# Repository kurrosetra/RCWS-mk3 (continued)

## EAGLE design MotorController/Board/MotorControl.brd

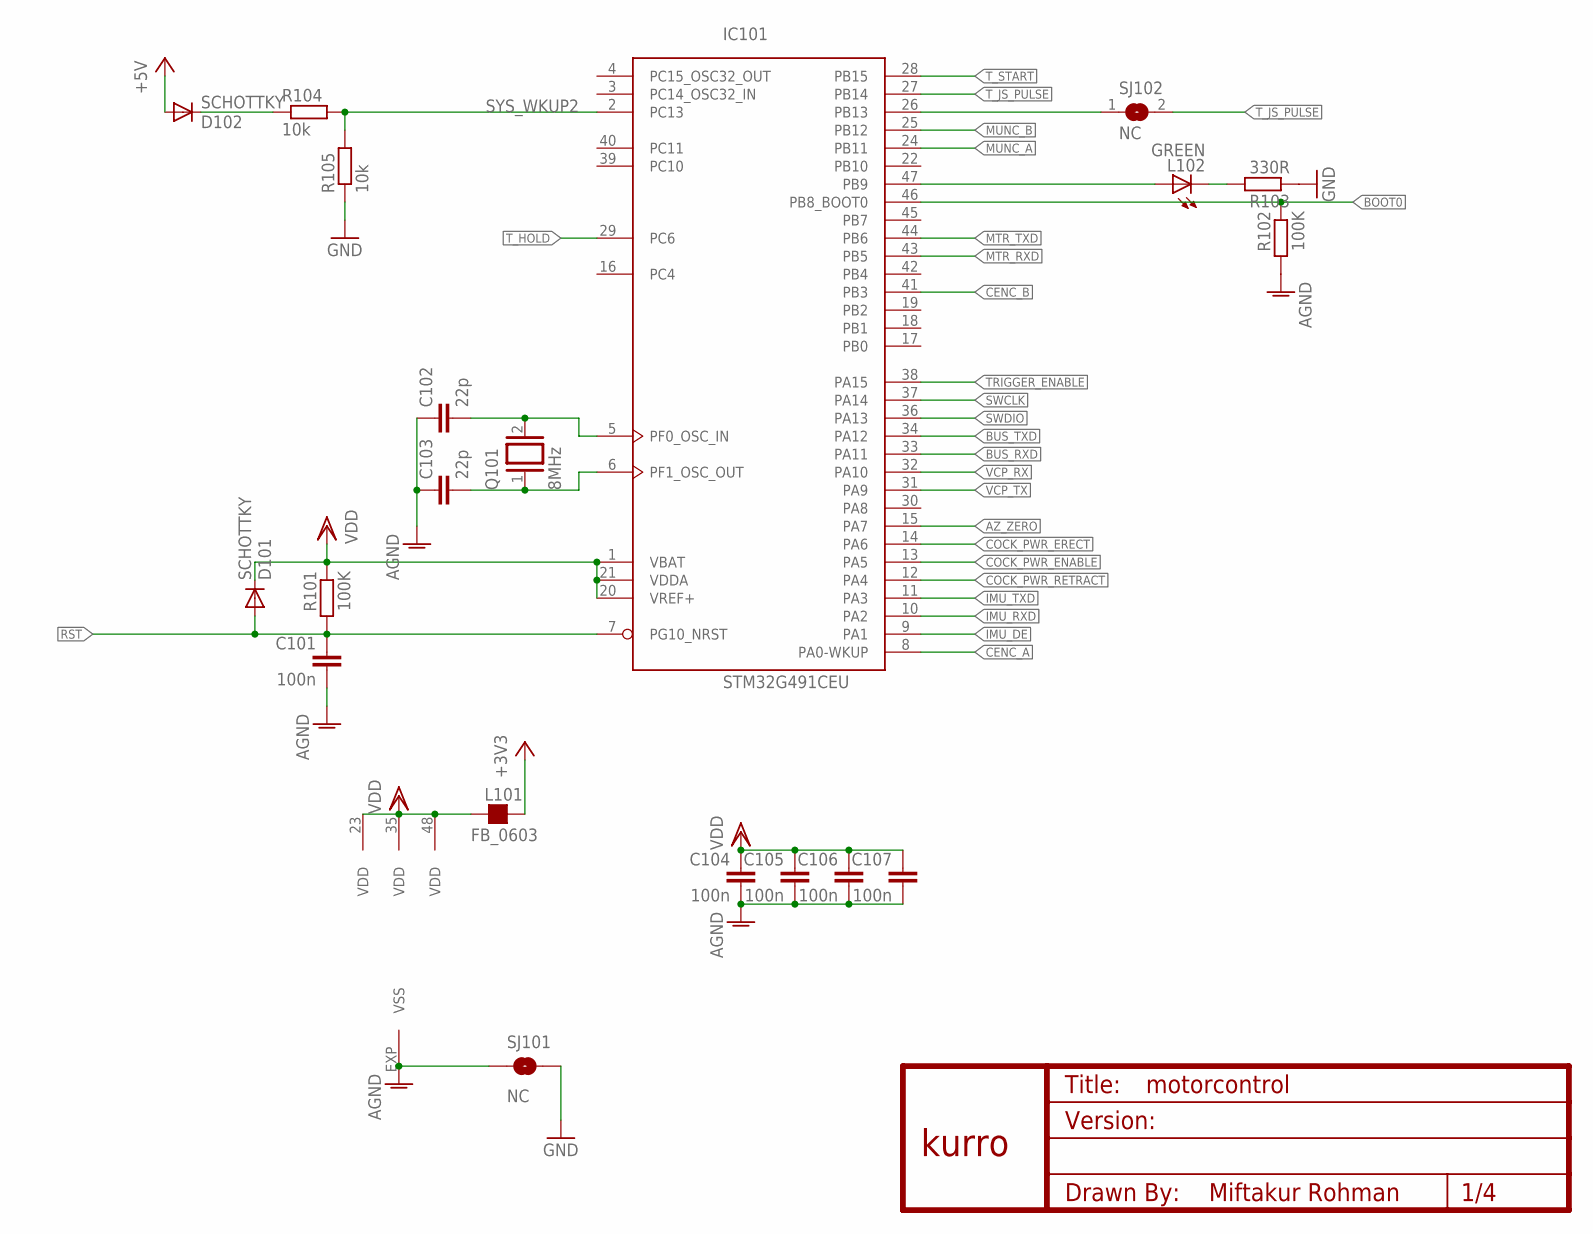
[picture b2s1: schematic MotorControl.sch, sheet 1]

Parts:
C101, C104, C105, C106, C107: 100n; C0603
C102, C103: 22p; C0603
D101, D102: SCHOTTKY; MICROMELF-W
IC101: STM32G491CEU; UFQFPN48
L101: FB_0603; L0603
L102: GREEN; CHIP-LED0805
Q101: 8MHz; QS
R101, R102: 100K; R0603
R103: 330R; R0603
R104, R105: 10k; R0603
SJ101: NC; SJ_2S-TRACE_THICK
SJ102: NC; SJS
U$1: KURRO_FOOTPRINT; KURRO-LOGO

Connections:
!RST: C101.1, D101.A, IC101.7 (PG10_NRST), R101.2; also elsewhere on the board
+3V3: L101.2; also elsewhere on the board
+5V: D102.A; also elsewhere on the board
AGND: C101.2, C102.1, C103.1, C104.2, C105.2, C106.2, C107.2, IC101.EXP (VSS), R102.2, SJ101.1
AZ_ZERO: IC101.15 (PA7); also elsewhere on the board
BOOT0: IC101.46 (PB8_BOOT0), R102.1; also elsewhere on the board
BUS_RXD: IC101.33 (PA11); also elsewhere on the board
BUS_TXD: IC101.34 (PA12); also elsewhere on the board
CENC_A: IC101.8 (PA0-WKUP); also elsewhere on the board
CENC_B: IC101.41 (PB3); also elsewhere on the board
COCK_PWR_ENABLE: IC101.13 (PA5); also elsewhere on the board
COCK_PWR_ERECT: IC101.14 (PA6); also elsewhere on the board
COCK_PWR_RETRACT: IC101.12 (PA4); also elsewhere on the board
GND: R103.1, R105.1, SJ101.2; also elsewhere on the board
IMU_DE: IC101.9 (PA1); also elsewhere on the board
IMU_RXD: IC101.10 (PA2); also elsewhere on the board
IMU_TXD: IC101.11 (PA3); also elsewhere on the board
MTR_RXD: IC101.43 (PB5); also elsewhere on the board
MTR_TXD: IC101.44 (PB6); also elsewhere on the board
MUNC_A: IC101.24 (PB11); also elsewhere on the board
MUNC_B: IC101.25 (PB12); also elsewhere on the board
unnamed: IC101.47 (PB9), L102.A
unnamed: L102.C, R103.2
unnamed: D102.C, R104.1
unnamed: C103.2, IC101.6 (PF1_OSC_OUT), Q101.1
unnamed: IC101.26 (PB13), SJ102.1
unnamed: C102.2, IC101.5 (PF0_OSC_IN), Q101.2
SWCLK: IC101.37 (PA14); also elsewhere on the board
SWDIO: IC101.36 (PA13); also elsewhere on the board
SYS_WKUP2: IC101.2 (PC13), R104.2, R105.2
TRIGGER_ENABLE: IC101.38 (PA15); also elsewhere on the board
T_HOLD: IC101.29 (PC6); also elsewhere on the board
T_JS_PULSE: IC101.27 (PB14), SJ102.2; also elsewhere on the board
T_START: IC101.28 (PB15); also elsewhere on the board
VCP_RX: IC101.32 (PA10); also elsewhere on the board
VCP_TX: IC101.31 (PA9); also elsewhere on the board
VDD: C104.1, C105.1, C106.1, C107.1, D101.C, IC101.1 (VBAT), IC101.20 (VREF+), IC101.21 (VDDA), IC101.23 (VDD), IC101.35 (VDD), IC101.48 (VDD), L101.1, R101.1; also elsewhere on the board

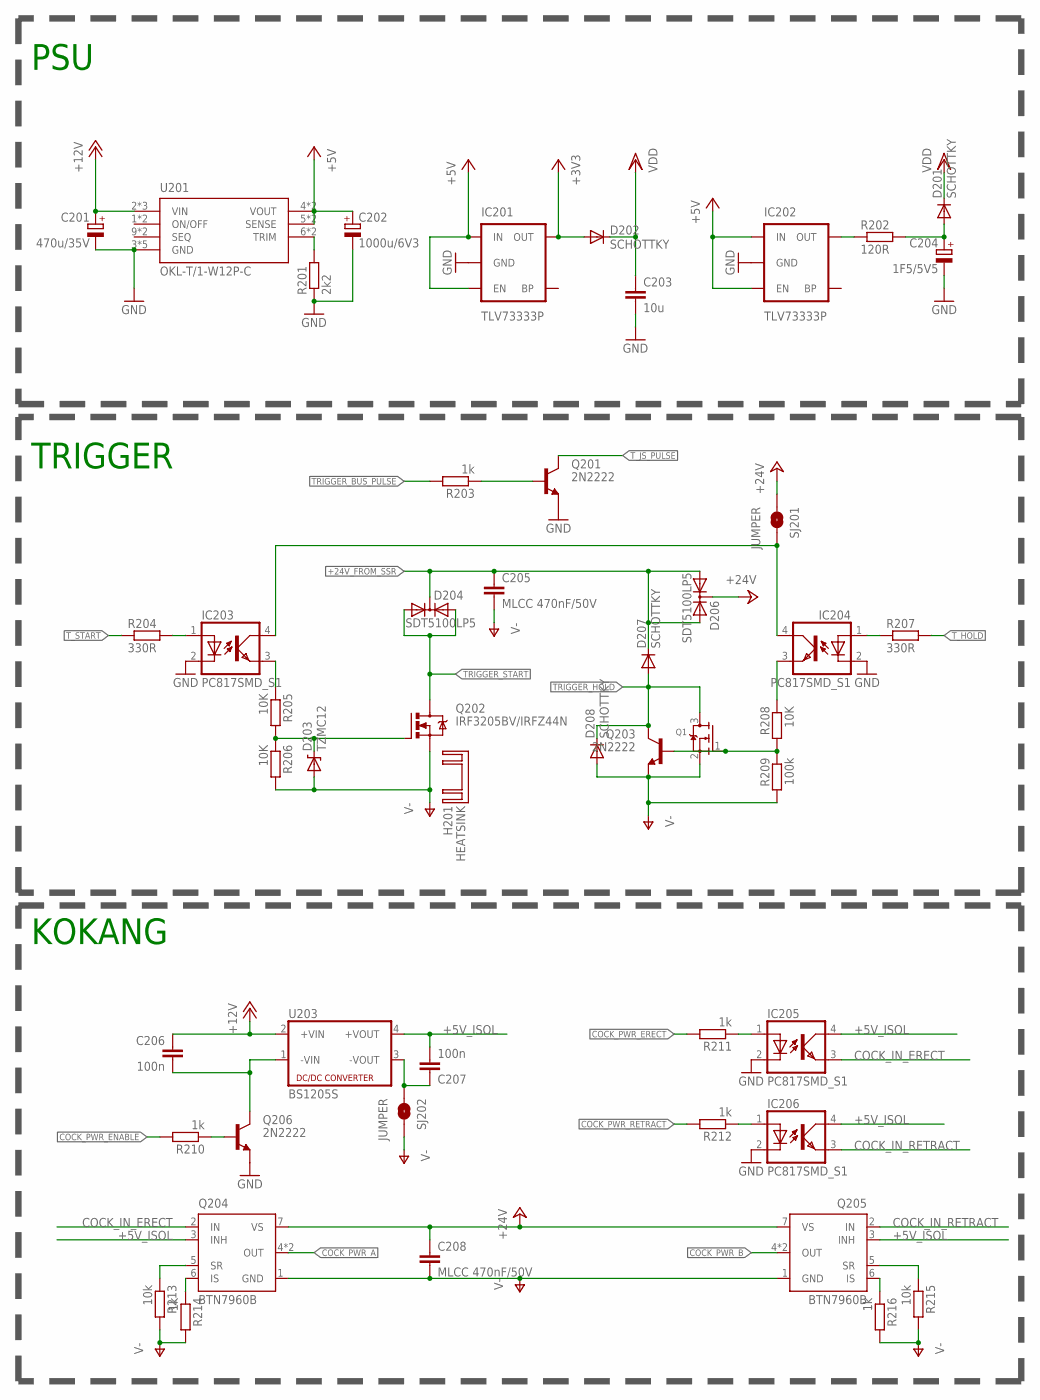
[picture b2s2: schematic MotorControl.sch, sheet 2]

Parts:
C201: 470u/35V; 153CLV-1012
C202: 1000u/6V3; 153CLV-0810
C203: 10u; C0805
C204: 1F5/5V5; SC_1F/5V5
C205, C208: MLCC 470nF/50V; C150-064X183
C206, C207: 100n; C0603
D201, D202, D207, D208: SCHOTTKY; MICROMELF-W
D203: TZMC12; SMB-DIODE
D204, D206: SDT5100LP5; POWERDI5-3
H201: HEATSINK; BV_240X170-HOLE
IC201, IC202: TLV73333P; SOT23-5
IC203, IC204, IC205, IC206: PC817SMD_S1; PC817SMD
Q1: AO3404-REFLOW; SOT23
Q201, Q203, Q206: 2N2222; SOT23
Q202: IRF3205BV/IRFZ44N; TO220BV
Q204: BTN7960B; PG-TO263-7-1; PARTNO BTN7960B
Q205: BTN7960B; PG-TO263-7-1
R201: 2k2; R0603
R202: 120R; R0603
R203, R210, R211, R212, R214, R216: 1k; R0603
R204, R207: 330R; R0603
R205, R206, R208: 10K; R0603
R209: 100k; R0603
R213, R215: 10k; R0603
SJ201, SJ202: JUMPER; SJ_2S-TRACE_THICK
U201: OKL-T/1-W12P-C; OKL2T/3W5NC
U203: BS1205S; NME

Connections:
+3V3: D202.A, IC201.5 (OUT); also elsewhere on the board
+5V: C202.+, IC201.1 (IN), IC201.3 (EN), IC202.1 (IN), IC202.3 (EN), U201.4 (VOUT), U201.4@1 (VOUT), U201.5 (SENSE), U201.5@1 (SENSE); also elsewhere on the board
+5V_ISOL: C207.2, IC205.4 (COL), IC206.4 (COL), Q204.3 (INH), Q205.3 (INH), U203.4 (+VOUT)
+12V: C201.+, C206.1, U201.2 (VIN), U201.2@1 (VIN), U201.2@2 (VIN), U203.2 (+VIN); also elsewhere on the board
+24V: C208.1, D206.3, Q204.7 (VS), Q205.7 (VS), SJ201.1; also elsewhere on the board
+24V_FROM_SSR: C205.1, D204.3, D206.1, D206.2, D207.C; also elsewhere on the board
COCK_IN_ERECT: IC205.3 (EMIT), Q204.2 (IN)
COCK_IN_RETRACT: IC206.3 (EMIT), Q205.2 (IN)
COCK_PWR_A: Q204.4 (OUT), Q204.8 (OUT); also elsewhere on the board
COCK_PWR_B: Q205.4 (OUT), Q205.8 (OUT); also elsewhere on the board
COCK_PWR_ENABLE: R210.2; also elsewhere on the board
COCK_PWR_ERECT: R211.2; also elsewhere on the board
COCK_PWR_RETRACT: R212.2; also elsewhere on the board
COCK_SENSOR1: Q204.6 (IS), R214.1
GND: C201.-, C202.-, C203.2, C204.2 (-), IC201.2 (GND), IC202.2 (GND), IC203.2 (C), IC204.2 (C), IC205.2 (C), IC206.2 (C), Q201.2 (E), Q206.2 (E), R201.1, U201.3 (GND), U201.3@1 (GND), U201.3@2 (GND), U201.7 (GND), U201.7@1 (GND); also elsewhere on the board
unnamed: IC203.4 (COL), IC204.4 (COL), SJ201.2
unnamed: Q204.5 (SR), R213.1
unnamed: Q205.5 (SR), R215.1
unnamed: Q205.6 (IS), R216.1
unnamed: Q206.1 (B), R210.1
unnamed: C206.2, Q206.3 (C), U203.1 (-VIN)
unnamed: Q201.1 (B), R203.1
unnamed: IC205.1 (A), R211.1
unnamed: R201.2, U201.6 (TRIM), U201.6@1 (TRIM)
unnamed: IC206.1 (A), R212.1
unnamed: C207.1, SJ202.1, U203.3 (-VOUT)
unnamed: D203.C, Q202.G, R205.2, R206.1
unnamed: Q1.1 (G), Q203.1 (B), R208.2, R209.1
unnamed: IC203.3 (EMIT), R205.1
unnamed: IC204.3 (EMIT), R208.1
unnamed: IC204.1 (A), R207.1
unnamed: IC203.1 (A), R204.2
unnamed: IC202.5 (OUT), R202.1
TRIGGER_BUS_PULSE: R203.2; also elsewhere on the board
TRIGGER_HOLD: D207.A, D208.C, Q1.3 (D), Q203.3 (C); also elsewhere on the board
TRIGGER_START: D204.1, D204.2, Q202.D; also elsewhere on the board
T_HOLD: R207.2; also elsewhere on the board
T_JS_PULSE: Q201.3 (C); also elsewhere on the board
T_START: R204.1; also elsewhere on the board
V-: C205.2, C208.2, D203.A, D208.A, Q1.2 (S), Q202.S, Q203.2 (E), Q204.1 (GND), Q205.1 (GND), R206.2, R209.2, R213.2, R214.2, R215.2, R216.2, SJ202.2; also elsewhere on the board
VDD: C203.1, D201.C, D202.C; also elsewhere on the board
V_SCAP: C204.1 (+), D201.A, R202.2

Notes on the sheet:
KOKANG
TRIGGER
PSU

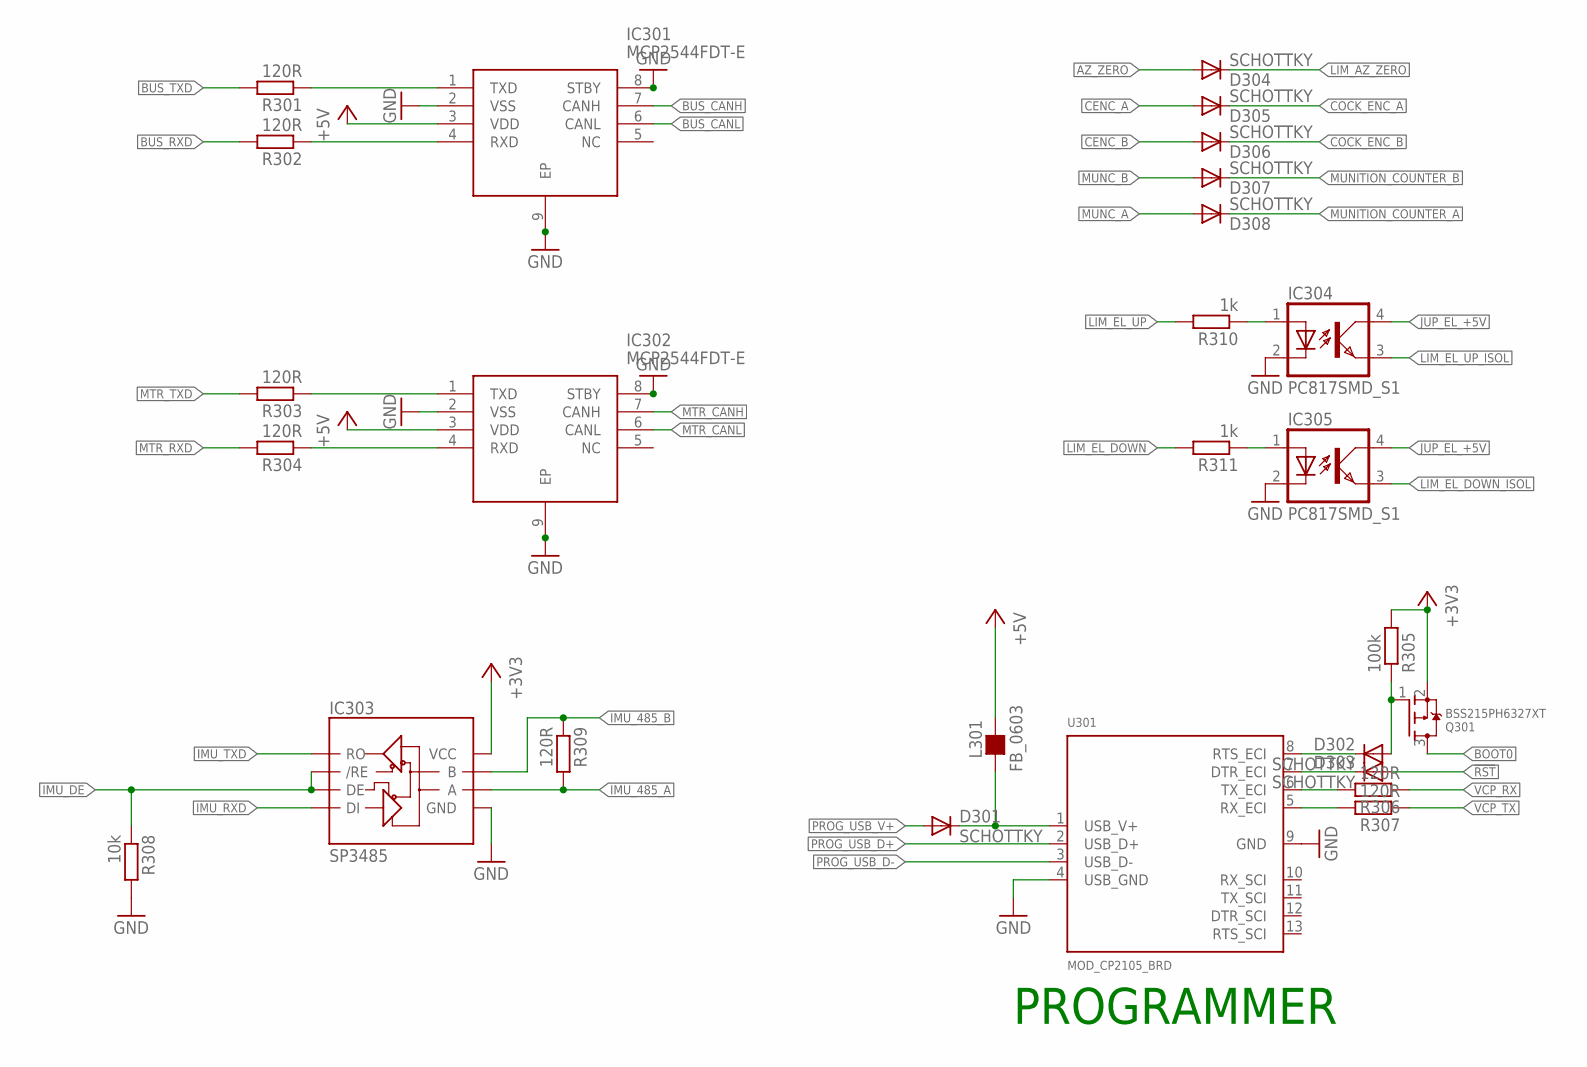
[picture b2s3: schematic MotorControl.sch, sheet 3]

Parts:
D301, D302, D303, D304, D305, D306, D307, D308: SCHOTTKY; MICROMELF-W
IC301, IC302: MCP2544FDT-E; TDFN-8
IC303: SP3485; SO08
IC304, IC305: PC817SMD_S1; PC817SMD
L301: FB_0603; L0603
Q301: BSS215PH6327XT; SOT23-W
R301, R302, R303, R304, R306, R307, R309: 120R; R0603
R305: 100k; R0603
R308: 10k; R0603
R310, R311: 1k; R0603
U301: MOD_CP2105_BRD; MOD_CP2105_BOARD

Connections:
!RST: D303.A; also elsewhere on the board
+3V3: IC303.8 (VCC), Q301.2 (S), R305.2; also elsewhere on the board
+5V: IC301.3 (VDD), IC302.3 (VDD), L301.2; also elsewhere on the board
AZ_ZERO: D304.A; also elsewhere on the board
BOOT0: Q301.3 (D); also elsewhere on the board
BUS_CANH: IC301.7 (CANH); also elsewhere on the board
BUS_CANL: IC301.6 (CANL); also elsewhere on the board
BUS_RXD: R302.2; also elsewhere on the board
BUS_TXD: R301.2; also elsewhere on the board
CENC_A: D305.A; also elsewhere on the board
CENC_B: D306.A; also elsewhere on the board
COCK_ENC_A: D305.C; also elsewhere on the board
COCK_ENC_B: D306.C; also elsewhere on the board
GND: IC301.2 (VSS), IC301.8 (STBY), IC301.9 (EP), IC302.2 (VSS), IC302.8 (STBY), IC302.9 (EP), IC303.5 (GND), IC304.2 (C), IC305.2 (C), R308.2, U301.4 (USB_GND), U301.9 (GND); also elsewhere on the board
IMU_485_A: IC303.6 (A), R309.2; also elsewhere on the board
IMU_485_B: IC303.7 (B), R309.1; also elsewhere on the board
IMU_DE: IC303.2 (/RE), IC303.3 (DE), R308.1; also elsewhere on the board
IMU_RXD: IC303.4 (DI); also elsewhere on the board
IMU_TXD: IC303.1 (RO); also elsewhere on the board
JUP_EL_+5V: IC304.4 (COL), IC305.4 (COL); also elsewhere on the board
LIM_AZ_ZERO: D304.C; also elsewhere on the board
LIM_EL_DOWN: R311.2; also elsewhere on the board
LIM_EL_DOWN_ISOL: IC305.3 (EMIT); also elsewhere on the board
LIM_EL_UP: R310.2; also elsewhere on the board
LIM_EL_UP_ISOL: IC304.3 (EMIT); also elsewhere on the board
MTR_CANH: IC302.7 (CANH); also elsewhere on the board
MTR_CANL: IC302.6 (CANL); also elsewhere on the board
MTR_RXD: R304.2; also elsewhere on the board
MTR_TXD: R303.2; also elsewhere on the board
MUNC_A: D308.A; also elsewhere on the board
MUNC_B: D307.A; also elsewhere on the board
MUNITION_COUNTER_A: D308.C; also elsewhere on the board
MUNITION_COUNTER_B: D307.C; also elsewhere on the board
unnamed: IC304.1 (A), R310.1
unnamed: R307.2, U301.5 (RX_ECI)
unnamed: R306.2, U301.6 (TX_ECI)
unnamed: D303.C, U301.7 (DTR_ECI)
unnamed: D302.C, U301.8 (RTS_ECI)
unnamed: D301.C, L301.1, U301.1 (USB_V+)
unnamed: D302.A, Q301.1 (G), R305.1
unnamed: IC305.1 (A), R311.1
unnamed: IC301.4 (RXD), R302.1
unnamed: IC301.1 (TXD), R301.1
unnamed: IC302.4 (RXD), R304.1
unnamed: IC302.1 (TXD), R303.1
PROG_USB_D+: U301.2 (USB_D+); also elsewhere on the board
PROG_USB_D-: U301.3 (USB_D-); also elsewhere on the board
PROG_USB_V+: D301.A; also elsewhere on the board
VCP_RX: R306.1; also elsewhere on the board
VCP_TX: R307.1; also elsewhere on the board

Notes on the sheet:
PROGRAMMER

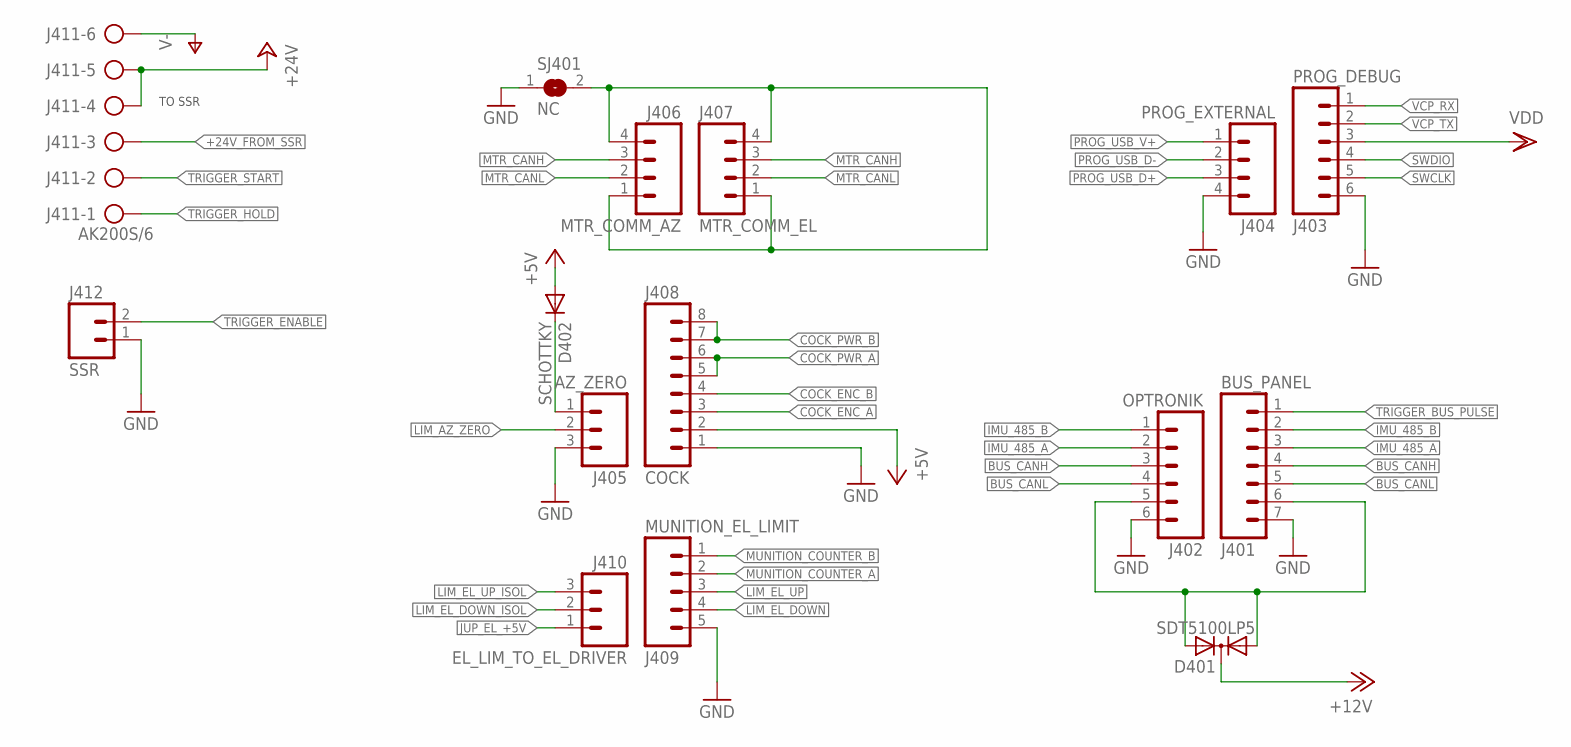
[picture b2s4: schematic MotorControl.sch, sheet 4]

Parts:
D401: SDT5100LP5; POWERDI5-3
D402: SCHOTTKY; MICROMELF-W
J401: BUS_PANEL; XHS-7-RA
J402: OPTRONIK; XHS-6-RA
J403: PROG_DEBUG; XHS-6-VERT-SMD
J404: PROG_EXTERNAL; XHS-4-RA
J405: AZ_ZERO; XHS-3-RA
J406: MTR_COMM_AZ; MICRO_MATCH_04
J407: MTR_COMM_EL; MICRO_MATCH_04
J408: COCK; XHS-8-RA
J409: MUNITION_EL_LIMIT; XHS-5-RA
J410: EL_LIM_TO_EL_DRIVER; XHS-3-RA
J411: AK200S/6
J412: SSR; XHS-2-RA
SJ401: NC; SJS

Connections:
+5V: D402.A, J408.2; also elsewhere on the board
+12V: D401.3; also elsewhere on the board
+24V: J411.4, J411.5; also elsewhere on the board
+24V_FROM_SSR: J411.3; also elsewhere on the board
BUS_CANH: J401.4, J402.3; also elsewhere on the board
BUS_CANL: J401.5, J402.4; also elsewhere on the board
COCK_ENC_A: J408.3; also elsewhere on the board
COCK_ENC_B: J408.4; also elsewhere on the board
COCK_PWR_A: J408.5, J408.6; also elsewhere on the board
COCK_PWR_B: J408.7, J408.8; also elsewhere on the board
GND: J401.7, J402.6, J403.6, J404.4, J405.3, J408.1, J409.5, J412.1, SJ401.1; also elsewhere on the board
IMU_485_A: J401.3, J402.2; also elsewhere on the board
IMU_485_B: J401.2, J402.1; also elsewhere on the board
JUP_EL_+5V: J410.1; also elsewhere on the board
LIM_AZ_ZERO: J405.2; also elsewhere on the board
LIM_EL_DOWN: J409.4; also elsewhere on the board
LIM_EL_DOWN_ISOL: J410.2; also elsewhere on the board
LIM_EL_UP: J409.3; also elsewhere on the board
LIM_EL_UP_ISOL: J410.3; also elsewhere on the board
MTR_CANH: J406.3, J407.3; also elsewhere on the board
MTR_CANL: J406.2, J407.2; also elsewhere on the board
MUNITION_COUNTER_A: J409.2; also elsewhere on the board
MUNITION_COUNTER_B: J409.1; also elsewhere on the board
unnamed: D402.C, J405.1
unnamed: J406.1, J406.4, J407.1, J407.4, SJ401.2
unnamed: D401.1, D401.2, J401.6, J402.5
PROG_USB_D+: J404.3; also elsewhere on the board
PROG_USB_D-: J404.2; also elsewhere on the board
PROG_USB_V+: J404.1; also elsewhere on the board
SWCLK: J403.5; also elsewhere on the board
SWDIO: J403.4; also elsewhere on the board
TRIGGER_BUS_PULSE: J401.1; also elsewhere on the board
TRIGGER_ENABLE: J412.2; also elsewhere on the board
TRIGGER_HOLD: J411.1; also elsewhere on the board
TRIGGER_START: J411.2; also elsewhere on the board
V-: J411.6; also elsewhere on the board
VCP_RX: J403.1; also elsewhere on the board
VCP_TX: J403.2; also elsewhere on the board
VDD: J403.3; also elsewhere on the board

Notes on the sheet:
TO SSR

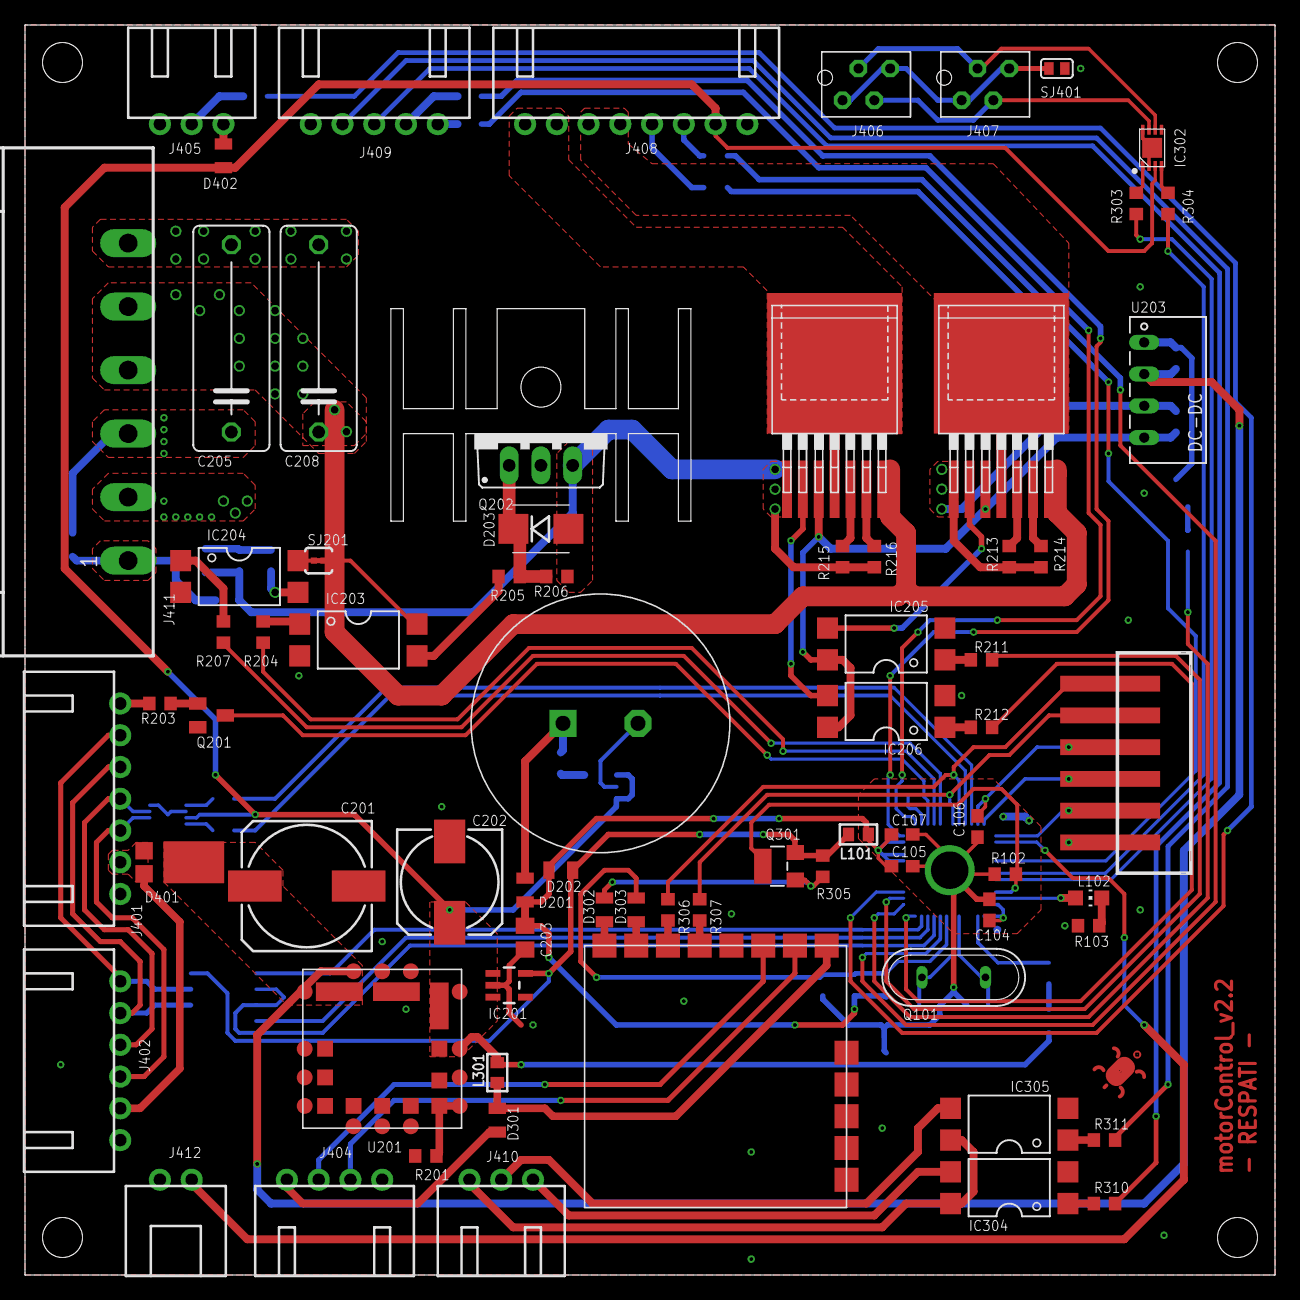
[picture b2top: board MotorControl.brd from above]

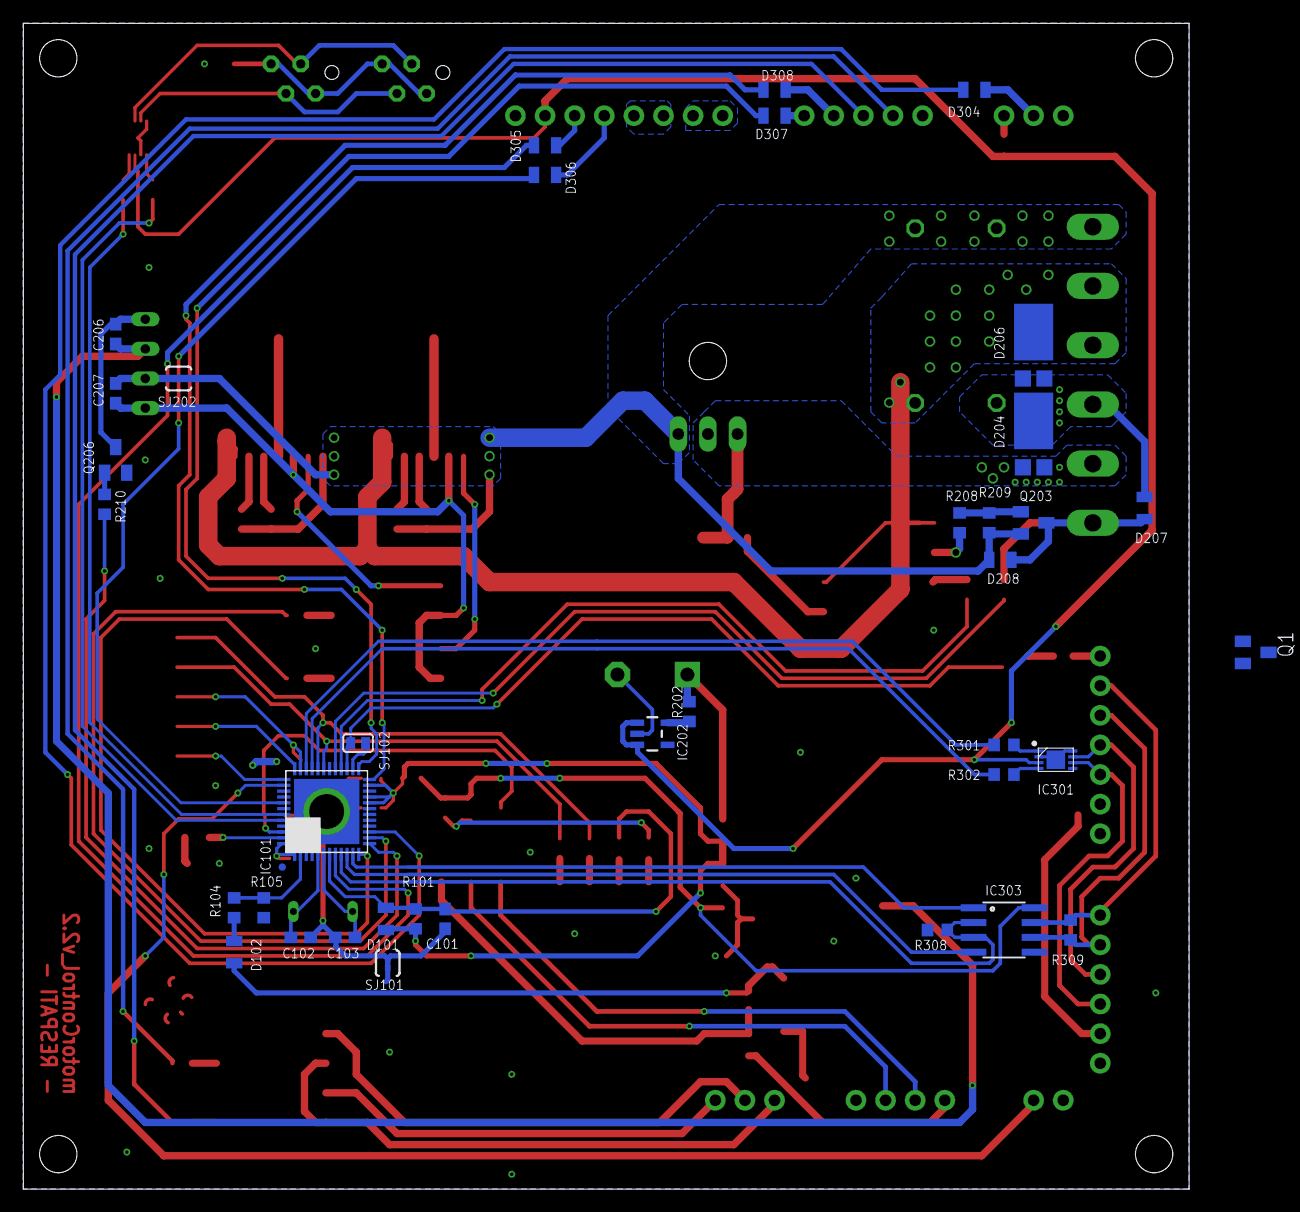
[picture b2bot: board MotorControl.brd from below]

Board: 2 copper layers, 100.0 x 100.0 mm, 112 parts (38 on the bottom side), 103 nets.

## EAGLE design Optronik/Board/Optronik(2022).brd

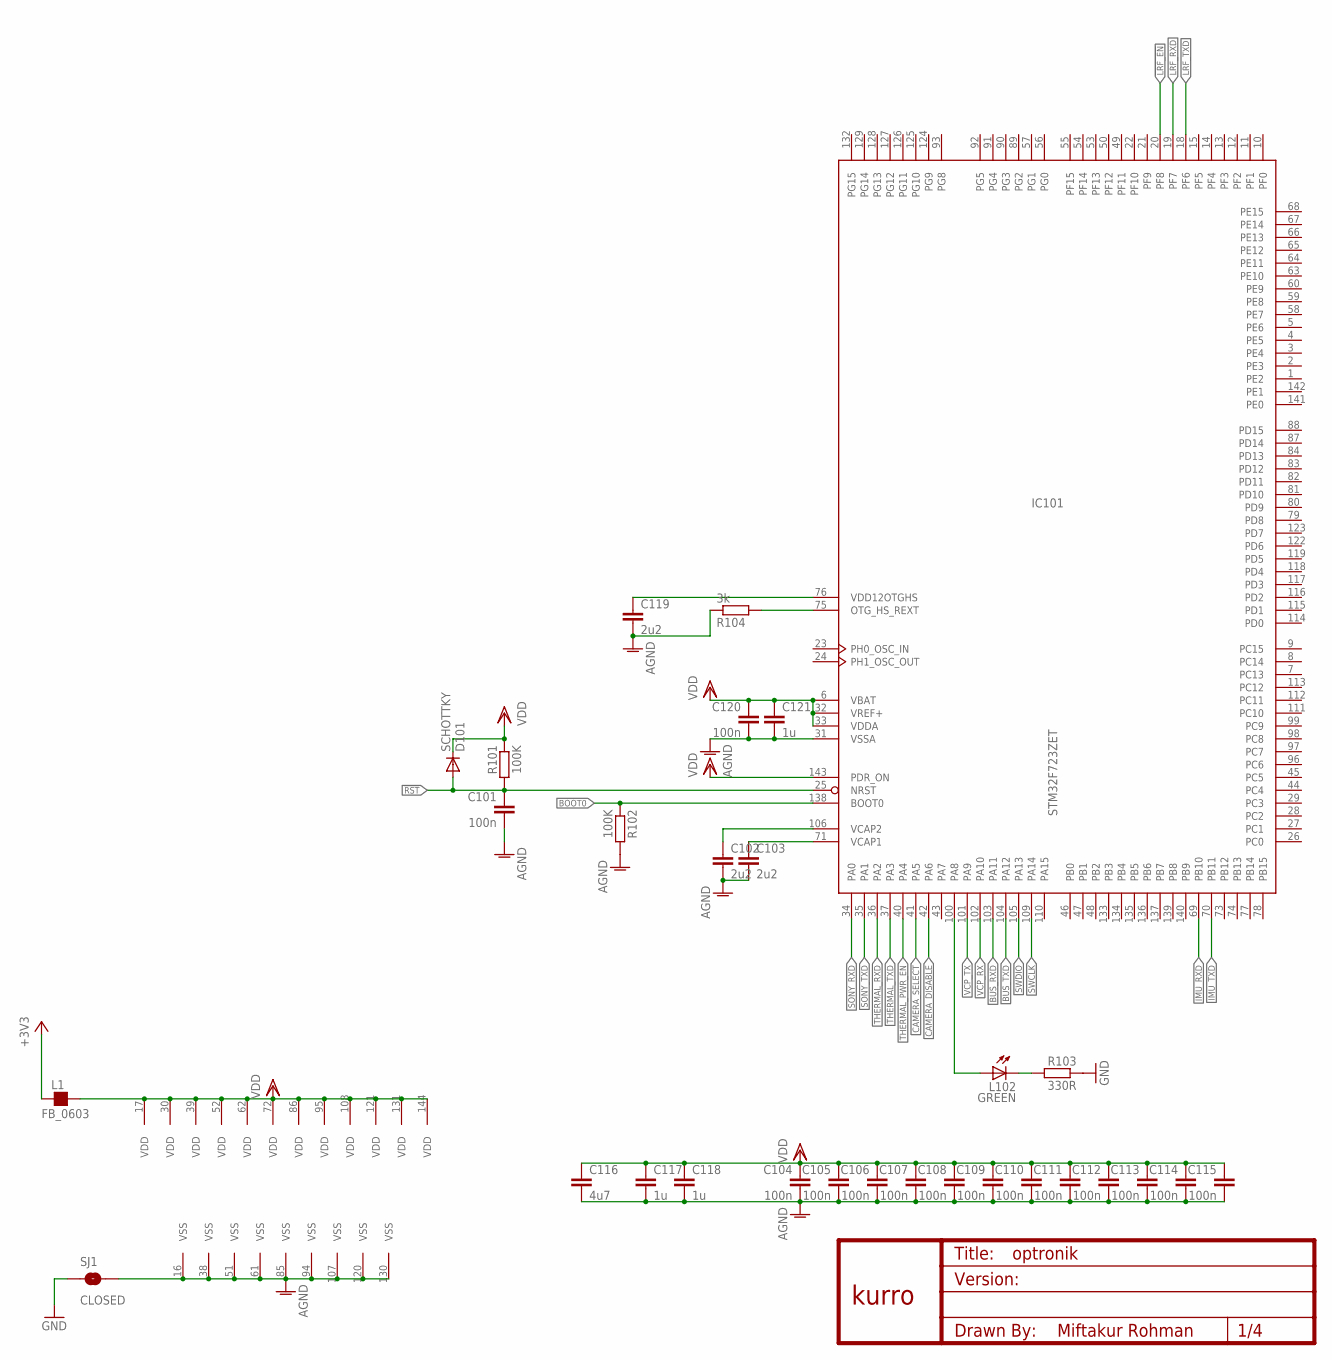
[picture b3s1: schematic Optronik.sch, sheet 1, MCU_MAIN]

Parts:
C101, C104, C105, C106, C107, C108, C109, C110, C111, C112, C113, C114, C115, C120: 100n; C0603
C102, C103, C119: 2u2; C0805
C116: 4u7; C0805
C117, C118, C121: 1u; C0805
D101: SCHOTTKY; MICROMELF-W
IC101: STM32F723ZET; LQFP144-2
L1: FB_0603; L0603
L102: GREEN; CHIP-LED0805
R101, R102: 100K; R0603
R103: 330R; R0603
R104: 3k; R0603
SJ1: CLOSED; SJ_2S-TRACE_THICK
U$2: KURRO_FOOTPRINT; KURRO-LOGO

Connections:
!LRF_EN: IC101.20 (PF8); also elsewhere on the board
!RST: C101.1, D101.A, IC101.25 (NRST), R101.2; also elsewhere on the board
+3V3: L1.1; also elsewhere on the board
AGND: C101.2, C102.2, C103.2, C104.2, C105.2, C106.2, C107.2, C108.2, C109.2, C110.2, C111.2, C112.2, C113.2, C114.2, C115.2, C116.2, C117.2, C118.2, C119.2, C120.2, C121.2, IC101.16 (VSS), IC101.31 (VSSA), IC101.38 (VSS), IC101.51 (VSS), IC101.61 (VSS), IC101.85 (VSS), IC101.94 (VSS), IC101.107 (VSS), IC101.120 (VSS), IC101.130 (VSS), R102.2, R104.1, SJ1.2
BOOT0: IC101.138 (BOOT0), R102.1; also elsewhere on the board
BUS_RXD: IC101.103 (PA11); also elsewhere on the board
BUS_TXD: IC101.104 (PA12); also elsewhere on the board
CAMERA_DISABLE: IC101.42 (PA6); also elsewhere on the board
CAMERA_SELECT: IC101.41 (PA5); also elsewhere on the board
GND: R103.1, SJ1.1; also elsewhere on the board
IMU_RXD: IC101.69 (PB10); also elsewhere on the board
IMU_TXD: IC101.70 (PB11); also elsewhere on the board
LRF_RXD: IC101.19 (PF7); also elsewhere on the board
LRF_TXD: IC101.18 (PF6); also elsewhere on the board
unnamed: IC101.75 (OTG_HS_REXT), R104.2
unnamed: IC101.100 (PA8), L102.A
unnamed: L102.C, R103.2
unnamed: C119.1, IC101.76 (VDD12OTGHS)
unnamed: C103.1, IC101.71 (VCAP1)
unnamed: C102.1, IC101.106 (VCAP2)
SONY_RXD: IC101.34 (PA0); also elsewhere on the board
SONY_TXD: IC101.35 (PA1); also elsewhere on the board
SWCLK: IC101.109 (PA14); also elsewhere on the board
SWDIO: IC101.105 (PA13); also elsewhere on the board
THERMAL_PWR_EN: IC101.40 (PA4); also elsewhere on the board
THERMAL_RXD: IC101.36 (PA2); also elsewhere on the board
THERMAL_TXD: IC101.37 (PA3); also elsewhere on the board
VCP_RX: IC101.102 (PA10); also elsewhere on the board
VCP_TX: IC101.101 (PA9); also elsewhere on the board
VDD: C104.1, C105.1, C106.1, C107.1, C108.1, C109.1, C110.1, C111.1, C112.1, C113.1, C114.1, C115.1, C116.1, C117.1, C118.1, C120.1, C121.1, D101.C, IC101.6 (VBAT), IC101.17 (VDD), IC101.30 (VDD), IC101.32 (VREF+), IC101.33 (VDDA), IC101.39 (VDD), IC101.52 (VDD), IC101.62 (VDD), IC101.72 (VDD), IC101.86 (VDD), IC101.95 (VDD), IC101.108 (VDD), IC101.121 (VDD), IC101.131 (VDD), IC101.143 (PDR_ON), IC101.144 (VDD), L1.2, R101.1; also elsewhere on the board

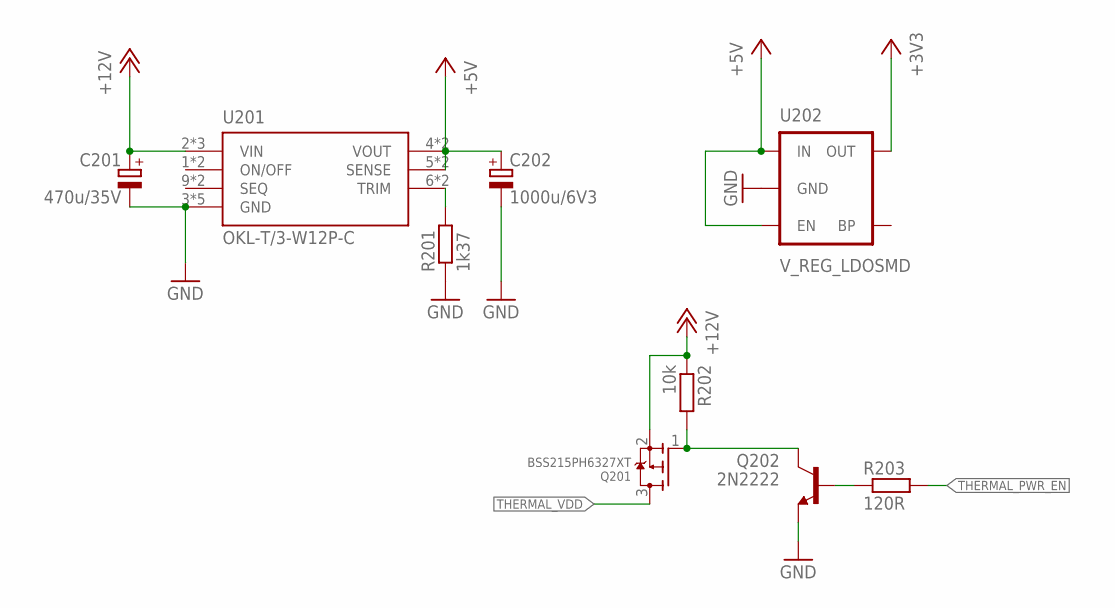
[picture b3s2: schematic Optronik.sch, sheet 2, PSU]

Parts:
C201: 470u/35V; 153CLV-1012
C202: 1000u/6V3; 153CLV-0810
Q201: BSS215PH6327XT; SOT23-W
Q202: 2N2222; SOT23
R201: 1k37; R0603
R202: 10k; R0603
R203: 120R; R0603
U201: OKL-T/3-W12P-C; OKL2T/3W5NC
U202: V_REG_LDOSMD; SOT23-5

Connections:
+3V3: U202.5 (OUT); also elsewhere on the board
+5V: C202.+, U201.4 (VOUT), U201.4@1 (VOUT), U201.5 (SENSE), U201.5@1 (SENSE), U202.1 (IN), U202.3 (EN); also elsewhere on the board
+12V: C201.+, Q201.2 (S), R202.1, U201.2 (VIN), U201.2@1 (VIN), U201.2@2 (VIN); also elsewhere on the board
GND: C201.-, C202.-, Q202.2 (E), R201.1, U201.3 (GND), U201.3@1 (GND), U201.3@2 (GND), U201.7 (GND), U201.7@1 (GND), U202.2 (GND); also elsewhere on the board
unnamed: R201.2, U201.6 (TRIM), U201.6@1 (TRIM)
unnamed: Q202.1 (B), R203.1
unnamed: Q201.1 (G), Q202.3 (C), R202.2
THERMAL_PWR_EN: R203.2; also elsewhere on the board
THERMAL_VDD: Q201.3 (D); also elsewhere on the board
